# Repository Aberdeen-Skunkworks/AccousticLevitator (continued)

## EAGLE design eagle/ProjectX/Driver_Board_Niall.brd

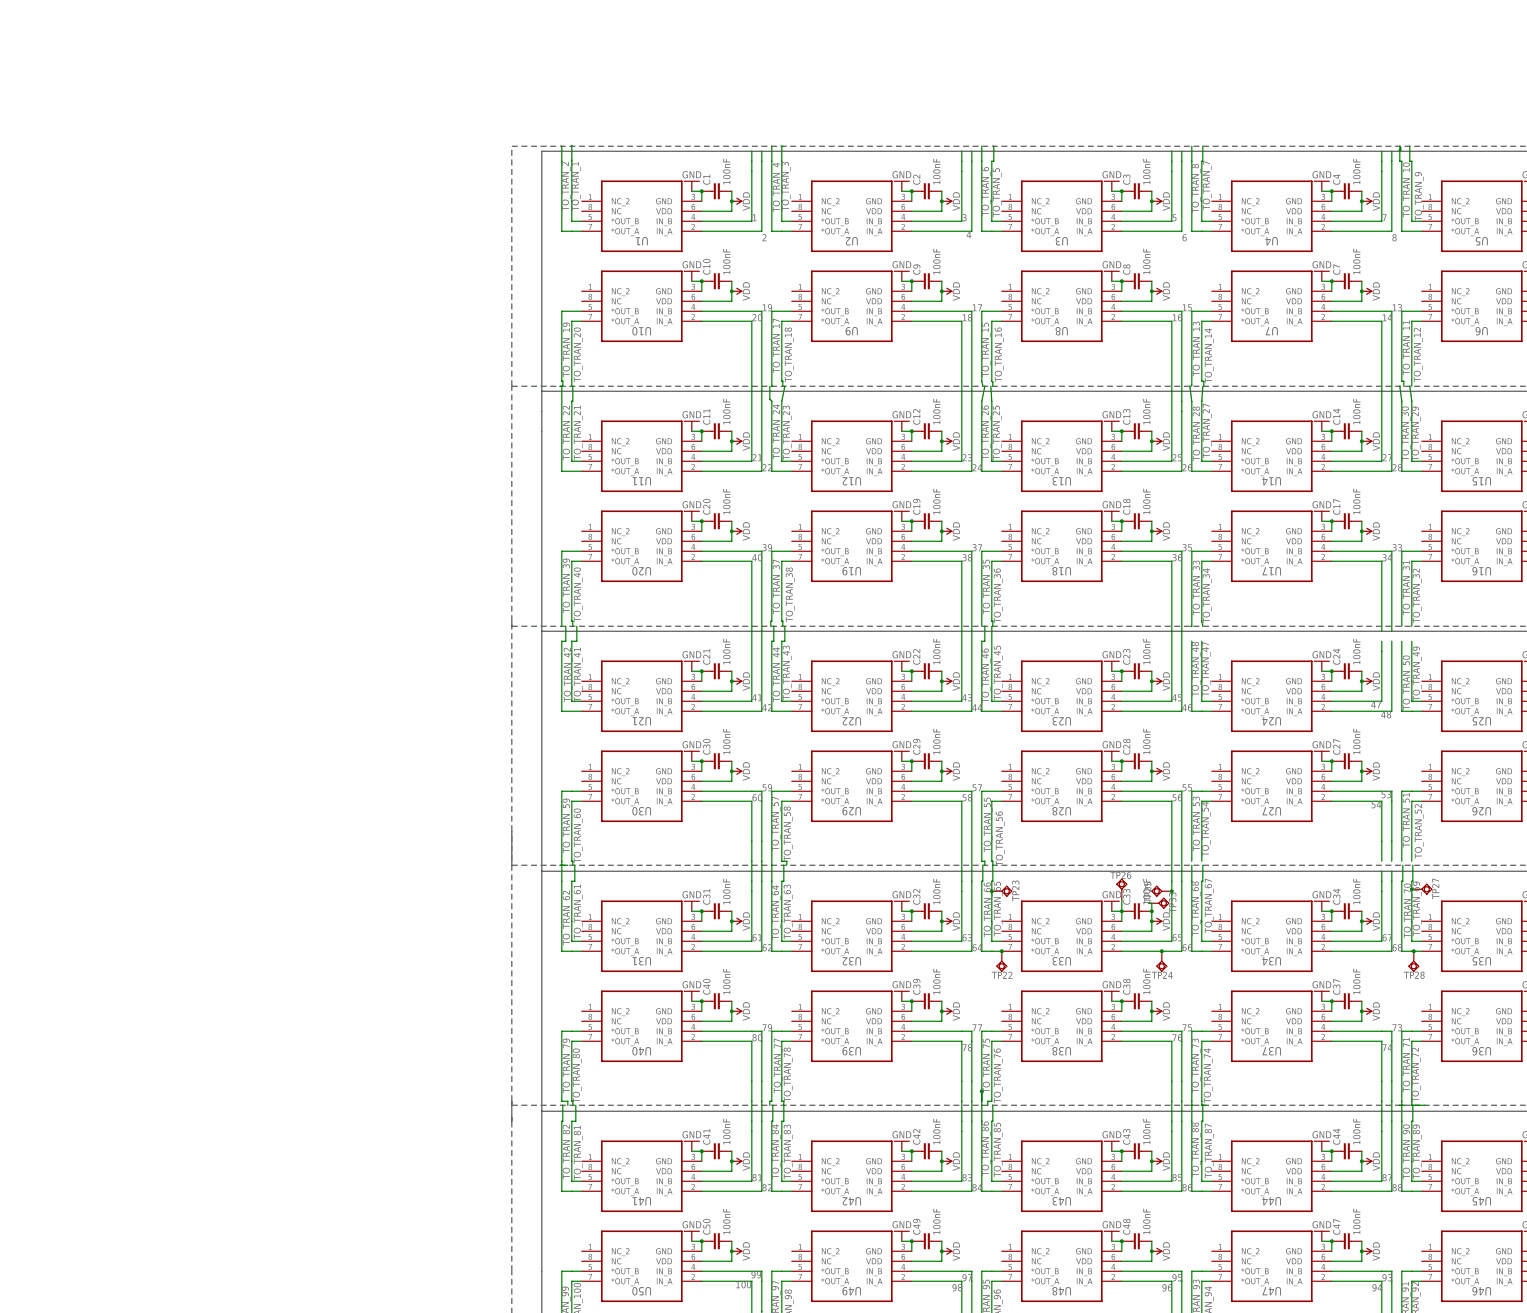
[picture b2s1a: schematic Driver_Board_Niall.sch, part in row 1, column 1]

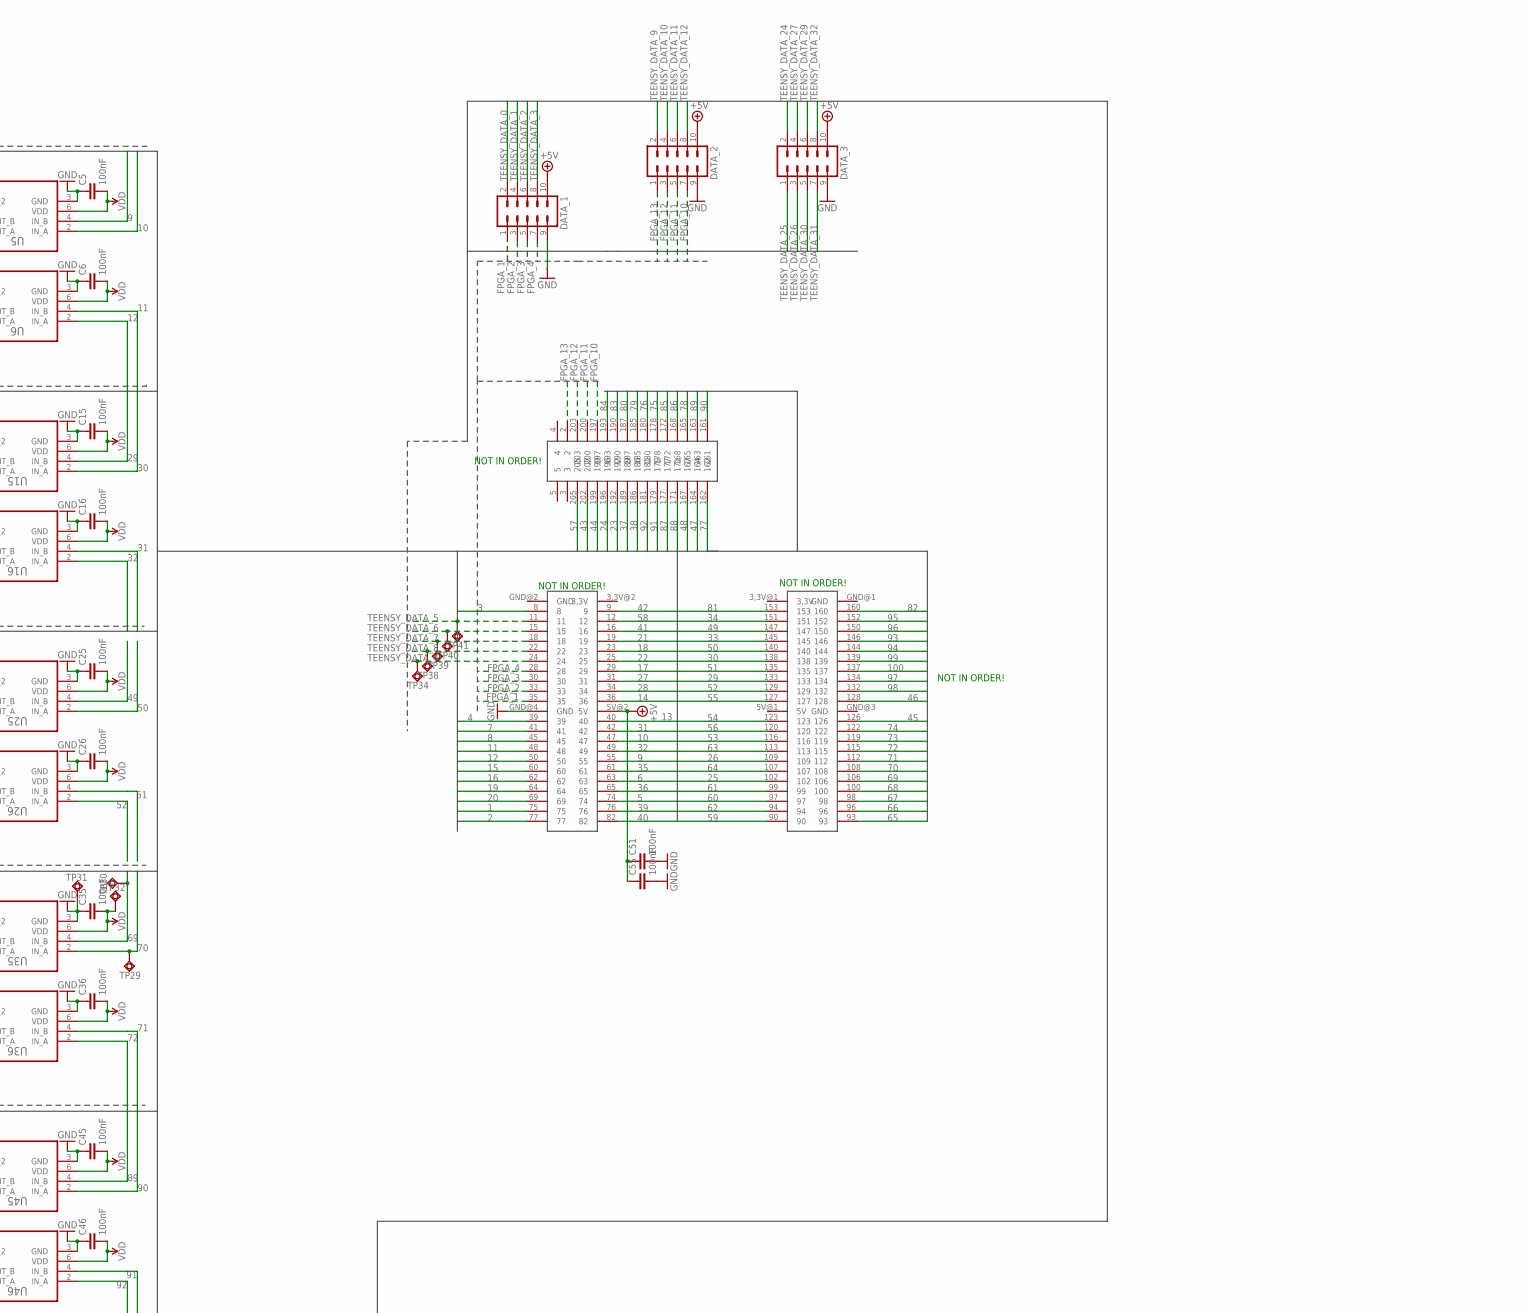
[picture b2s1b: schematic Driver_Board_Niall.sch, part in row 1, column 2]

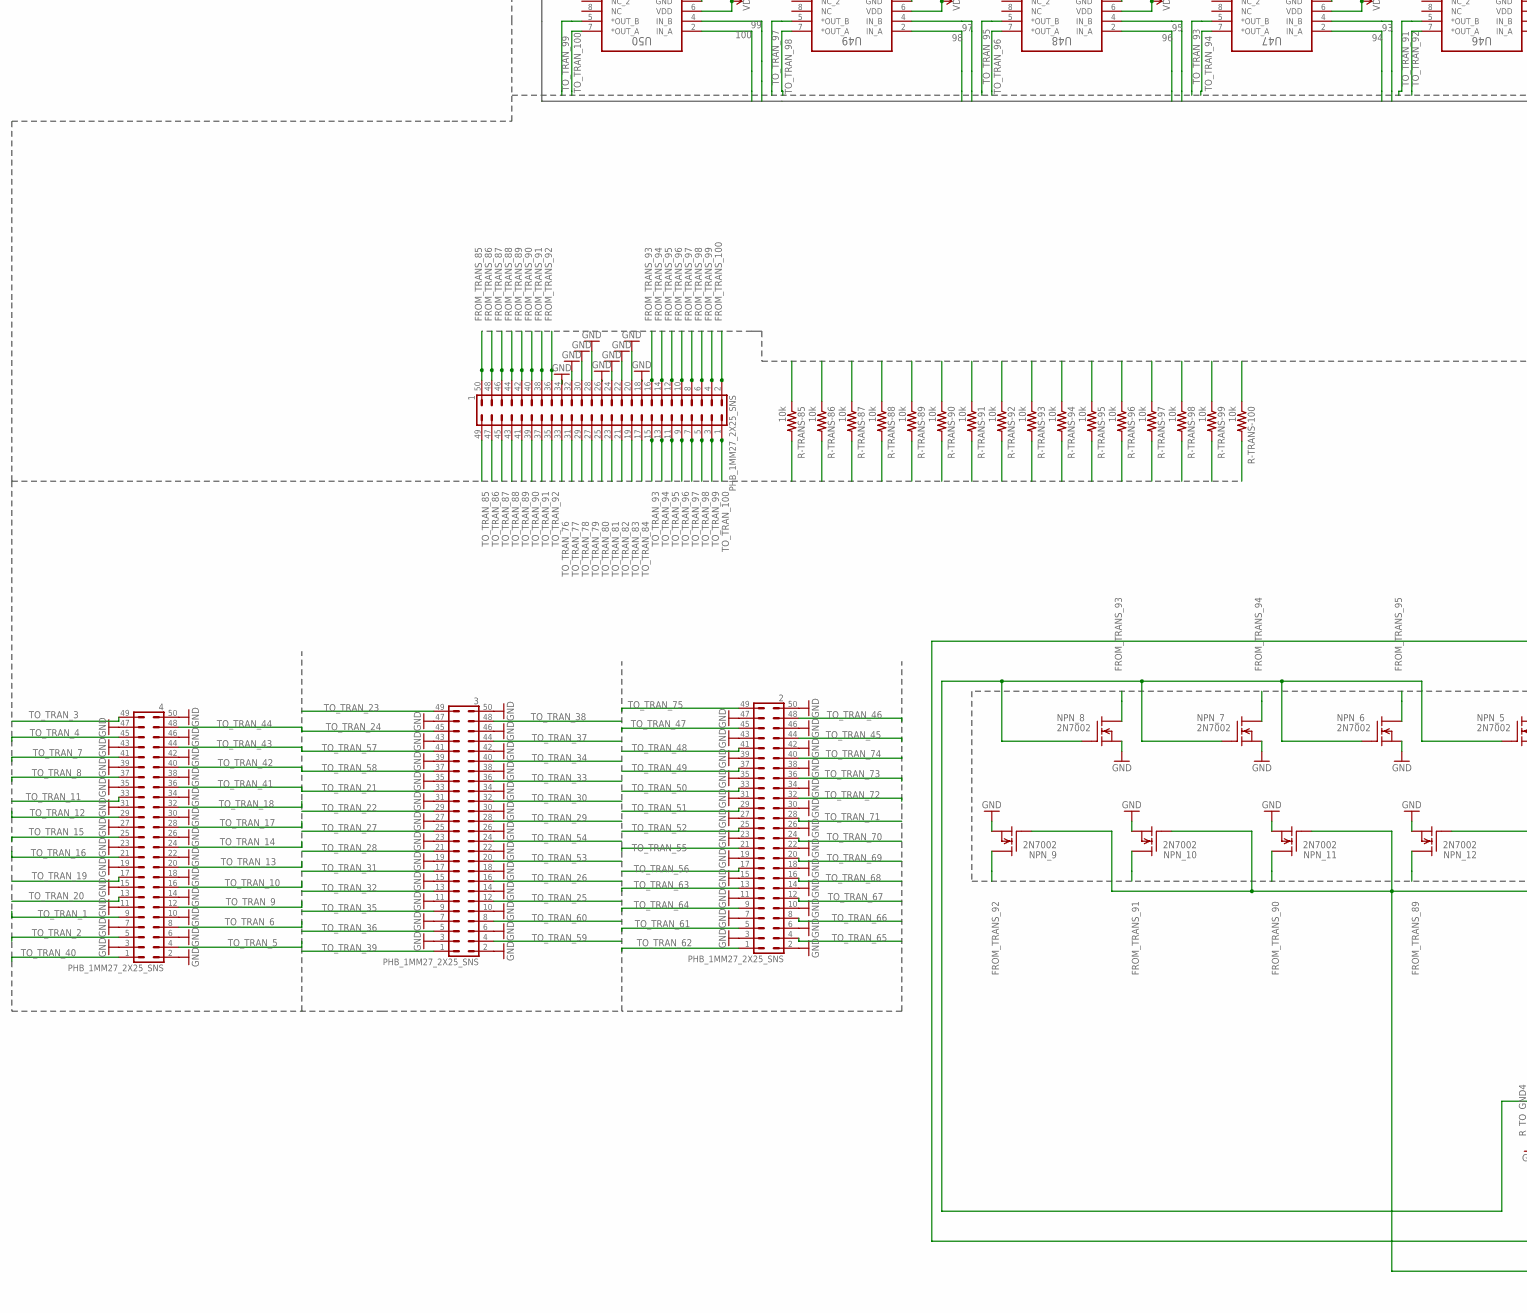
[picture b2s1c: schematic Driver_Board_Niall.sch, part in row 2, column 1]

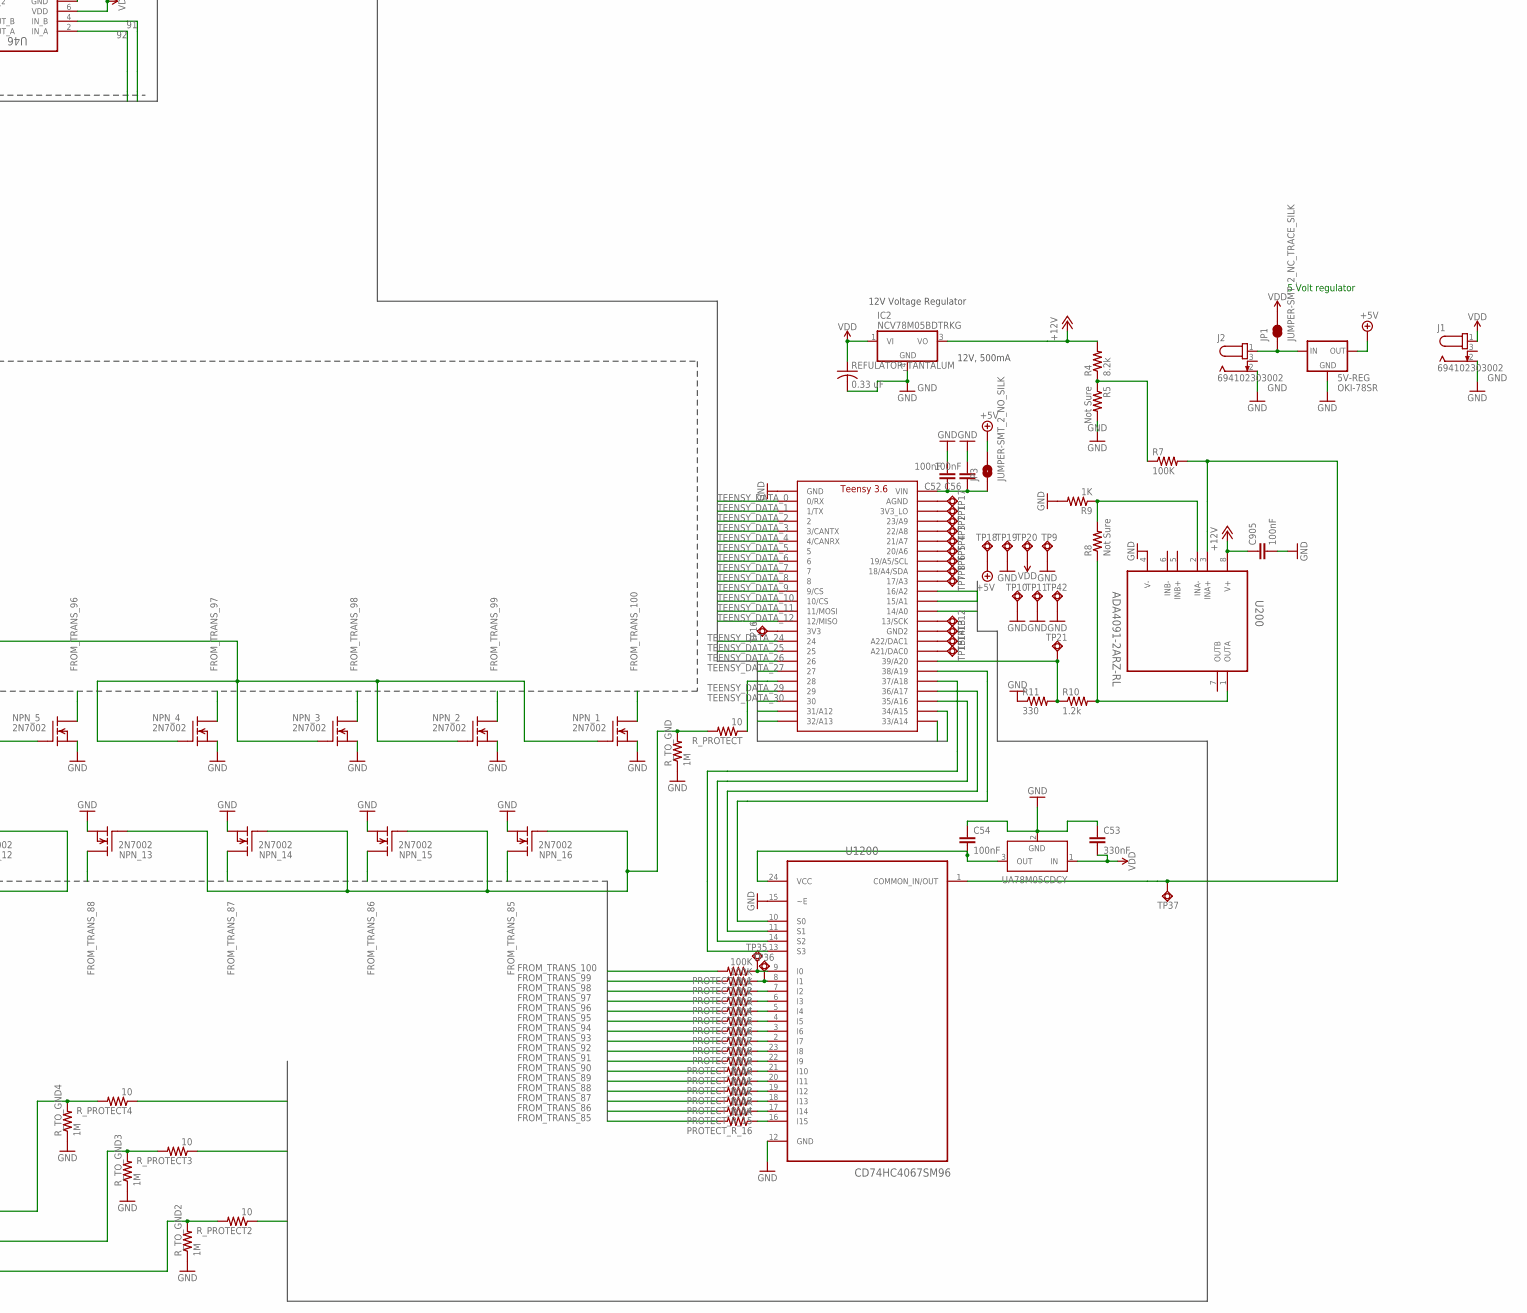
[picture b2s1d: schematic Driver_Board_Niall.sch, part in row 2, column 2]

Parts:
1, 2, 3, 4: PHB_1MM27_2X25_SNS
5V-REG: OKI-78SR; OKI-78SR-HORIZ
C1, C2, C3, C4, C5, C6, C7, C8, C9, C10, C11, C12, C13, C14, C15, C16, C17, C18, C19, C20, C21, C22, C23, C24, C25, C26, C27, C28, C29, C30, C31, C32, C33, C34, C35, C36, C37, C38, C39, C40, C41, C42, C43, C44, C45, C46, C47, C48, C49, C50, C51, C52, C54, C55, C56, C905: 100nF; C0805
C53: 330nF; C0805
DATA_1, DATA_2, DATA_3: MA05-2
DIP2: CORE3S500ESMT; CORE3S500E-SMT
IC2: NCV78M05BDTRKG; DPACK_3
J1, J2: 694102303002; 69410X303002
JP1: JUMPER-SMT_2_NC_TRACE_SILK; SMT-JUMPER_2_NC_TRACE_SILK
JP3: JUMPER-SMT_2_NO_SILK; SMT-JUMPER_2_NO_SILK
NPN_1, NPN_2, NPN_3, NPN_4, NPN_5, NPN_6, NPN_7, NPN_8, NPN_9, NPN_10, NPN_11, NPN_12, NPN_13, NPN_14, NPN_15, NPN_16: 2N7002; SOT23
PROTECT_R_1, PROTECT_R_2, PROTECT_R_3, PROTECT_R_4, PROTECT_R_5, PROTECT_R_6, PROTECT_R_7, PROTECT_R_8, PROTECT_R_9, PROTECT_R_10, PROTECT_R_11, PROTECT_R_12, PROTECT_R_13, PROTECT_R_14, PROTECT_R_15, PROTECT_R_16: 100K; M0805
R4: 8.2k; M0805
R5, R8: Not Sure; M0805
R7: 100K; M0805
R9: 1K; M0805
R10: 1.2k; M0805
R11: 330; M0805
R-TRANS-85, R-TRANS-86, R-TRANS-87, R-TRANS-88, R-TRANS-89, R-TRANS-90, R-TRANS-91, R-TRANS-92, R-TRANS-93, R-TRANS-94, R-TRANS-95, R-TRANS-96, R-TRANS-97, R-TRANS-98, R-TRANS-99, R-TRANS-100: 10k; M0805
REFULATOR_TANTALUM: 0.33 uF; C1206
R_PROTECT, R_PROTECT2, R_PROTECT3, R_PROTECT4: 10; M0805
R_TO_GND, R_TO_GND2, R_TO_GND3, R_TO_GND4: 1M; M0805
TP1, TP2, TP3, TP4, TP5, TP6, TP7, TP8, TP9, TP10, TP11, TP12, TP13, TP14, TP15, TP16, TP17, TP18, TP19, TP20, TP21, TP22, TP23, TP24, TP25, TP26, TP27, TP28, TP29, TP30, TP31, TP32, TP33, TP34, TP35, TP36, TP37, TP38, TP39, TP40, TP41, TP42: TPSQPAD1-13; P1-13
U1, U2, U3, U4, U5, U6, U7, U8, U9, U10, U11, U12, U13, U14, U15, U16, U17, U18, U19, U20, U21, U22, U23, U24, U25, U26, U27, U28, U29, U30, U31, U32, U33, U34, U35, U36, U37, U38, U39, U40, U41, U42, U43, U44, U45, U46, U47, U48, U49, U50: TC4427AEOA; SOIC127P600X175-8N
U200: ADA4091-2ARZ-RL; ADA4091-2ARZ-RL_SOIC127P600X175-8N
U1200: CD74HC4067SM96; SOP65P780X200-24N
U$1: TEENSY_SMD; TEENSY_3.6_SMD
UA78M05CDCY: LT1129CST5; SOT223

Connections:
1: DIP2.75, U1.4 (IN_B)
2: DIP2.77, U1.2 (IN_A)
3: DIP2.8, U2.4 (IN_B)
4: DIP2.39, U2.2 (IN_A)
5: DIP2.74, U3.4 (IN_B)
6: DIP2.63, U3.2 (IN_A)
7: DIP2.41, U4.4 (IN_B)
8: DIP2.45, U4.2 (IN_A)
9: DIP2.55, U5.4 (IN_B)
10: DIP2.47, U5.2 (IN_A)
11: DIP2.48, U6.4 (IN_B)
12: DIP2.50, U6.2 (IN_A)
13: DIP2.40, U7.4 (IN_B)
14: DIP2.36, U7.2 (IN_A)
15: DIP2.60, U8.4 (IN_B)
16: DIP2.62, U8.2 (IN_A)
17: DIP2.29, U9.4 (IN_B)
18: DIP2.23, U9.2 (IN_A)
19: DIP2.64, U10.4 (IN_B)
20: DIP2.69, U10.2 (IN_A)
21: DIP2.19, U11.4 (IN_B)
22: DIP2.25, U11.2 (IN_A)
23: DIP2.192, U12.4 (IN_B)
24: DIP2.196, U12.2 (IN_A)
25: DIP2.102, U13.4 (IN_B)
26: DIP2.109, U13.2 (IN_A)
27: DIP2.31, U14.4 (IN_B)
28: DIP2.34, U14.2 (IN_A)
29: DIP2.133, U15.4 (IN_B)
30: DIP2.138, U15.2 (IN_A)
31: DIP2.42, U16.4 (IN_B)
32: DIP2.49, U16.2 (IN_A)
33: DIP2.145, U17.4 (IN_B)
34: DIP2.151, U17.2 (IN_A)
35: DIP2.61, U18.4 (IN_B)
36: DIP2.65, U18.2 (IN_A)
37: DIP2.189, U19.4 (IN_B)
38: DIP2.186, U19.2 (IN_A)
39: DIP2.76, U20.4 (IN_B)
40: DIP2.82, U20.2 (IN_A)
41: DIP2.16, U21.4 (IN_B)
42: DIP2.9, U21.2 (IN_A)
43: DIP2.202, U22.4 (IN_B)
44: DIP2.199, U22.2 (IN_A)
45: DIP2.126, U23.4 (IN_B)
46: DIP2.128, U23.2 (IN_A)
47: DIP2.164, U24.4 (IN_B)
48: DIP2.167, U24.2 (IN_A)
49: DIP2.147, U25.4 (IN_B)
50: DIP2.140, U25.2 (IN_A)
51: DIP2.135, U26.4 (IN_B)
52: DIP2.129, U26.2 (IN_A)
53: DIP2.116, U27.4 (IN_B)
54: DIP2.123, U27.2 (IN_A)
55: DIP2.127, U28.4 (IN_B)
56: DIP2.120, U28.2 (IN_A)
57: DIP2.205, U29.4 (IN_B)
58: DIP2.12, U29.2 (IN_A)
59: DIP2.90, U30.4 (IN_B)
60: DIP2.97, U30.2 (IN_A)
61: DIP2.99, U31.4 (IN_B)
62: DIP2.94, U31.2 (IN_A)
63: DIP2.113, U32.4 (IN_B)
64: DIP2.107, U32.2 (IN_A)
65: DIP2.93, TP25.TP, U33.4 (IN_B)
66: DIP2.96, TP24.TP, U33.2 (IN_A)
67: DIP2.98, U34.4 (IN_B)
68: DIP2.100, U34.2 (IN_A)
69: DIP2.106, TP30.TP, U35.4 (IN_B)
70: DIP2.108, TP29.TP, U35.2 (IN_A)
71: DIP2.112, U36.4 (IN_B)
72: DIP2.115, U36.2 (IN_A)
73: DIP2.119, U37.4 (IN_B)
74: DIP2.122, U37.2 (IN_A)
75: DIP2.178, U38.4 (IN_B)
76: DIP2.180, U38.2 (IN_A)
77: DIP2.162, U39.4 (IN_B)
78: DIP2.165, U39.2 (IN_A)
79: DIP2.185, U40.4 (IN_B)
80: DIP2.187, U40.2 (IN_A)
81: DIP2.153, U41.4 (IN_B)
82: DIP2.160, U41.2 (IN_A)
83: DIP2.190, U42.4 (IN_B)
84: DIP2.193, U42.2 (IN_A)
85: DIP2.172, U43.4 (IN_B)
86: DIP2.168, U43.2 (IN_A)
87: DIP2.177, U44.4 (IN_B)
88: DIP2.171, U44.2 (IN_A)
89: DIP2.163, U45.4 (IN_B)
90: DIP2.161, U45.2 (IN_A)
91: DIP2.179, U46.4 (IN_B)
92: DIP2.181, U46.2 (IN_A)
93: DIP2.146, U47.4 (IN_B)
94: DIP2.144, U47.2 (IN_A)
95: DIP2.152, U48.4 (IN_B)
96: DIP2.150, U48.2 (IN_A)
97: DIP2.134, U49.4 (IN_B)
98: DIP2.132, U49.2 (IN_A)
99: DIP2.139, U50.4 (IN_B)
100: DIP2.137, U50.2 (IN_A)
+5V: 5V-REG.OUT, C51.1, C55.1, DATA_1.10, DATA_2.10, DATA_3.10, DIP2.5V@2 (5V), JP3.2, TP18.TP
+12V: C905.1, IC2.3 (VO), R4.2, U200.8 (V+)
FET_2: R_PROTECT2.1, U$1.16/A4 (16/A2)
FET_3: R_PROTECT3.1, U$1.15/A4 (15/A1)
FET_4: R_PROTECT4.1, U$1.14/A3 (14/A0)
FPGA_1: DATA_1.1, DIP2.35
FPGA_2: DATA_1.3, DIP2.33
FPGA_3: DATA_1.5, DIP2.30
FPGA_4: DATA_1.7, DIP2.28
FPGA_10: DATA_2.7, DIP2.197
FPGA_11: DATA_2.5, DIP2.200
FPGA_12: DATA_2.3, DIP2.203
FPGA_13: DATA_2.1, DIP2.2
FROM_TRANS_85: 1.50, NPN_16.3 (D), PROTECT_R_16.2, R-TRANS-85.1
FROM_TRANS_86: 1.48, NPN_15.3 (D), PROTECT_R_15.2, R-TRANS-86.1
FROM_TRANS_87: 1.46, NPN_14.3 (D), PROTECT_R_14.2, R-TRANS-87.1
FROM_TRANS_88: 1.44, NPN_13.3 (D), PROTECT_R_13.2, R-TRANS-88.1
FROM_TRANS_89: 1.42, NPN_12.3 (D), PROTECT_R_12.2, R-TRANS-89.1
FROM_TRANS_90: 1.40, NPN_11.3 (D), PROTECT_R_11.2, R-TRANS-90.1
FROM_TRANS_91: 1.38, NPN_10.3 (D), PROTECT_R_10.2, R-TRANS-91.1
FROM_TRANS_92: 1.36, NPN_9.3 (D), PROTECT_R_9.2, R-TRANS-92.1
FROM_TRANS_93: 1.16, NPN_8.3 (D), PROTECT_R_8.2, R-TRANS-93.1
FROM_TRANS_94: 1.14, NPN_7.3 (D), PROTECT_R_7.2, R-TRANS-94.1
FROM_TRANS_95: 1.12, NPN_6.3 (D), PROTECT_R_6.2, R-TRANS-95.1
FROM_TRANS_96: 1.10, NPN_5.3 (D), PROTECT_R_5.2, R-TRANS-96.1
FROM_TRANS_97: 1.8, NPN_4.3 (D), PROTECT_R_4.2, R-TRANS-97.1
FROM_TRANS_98: 1.6, NPN_3.3 (D), PROTECT_R_3.2, R-TRANS-98.1
FROM_TRANS_99: 1.4, NPN_2.3 (D), PROTECT_R_2.2, R-TRANS-99.1
FROM_TRANS_100: 1.2, NPN_1.3 (D), PROTECT_R_1.2, R-TRANS-100.1
GND: 1.18, 1.20, 1.22, 1.24, 1.26, 1.28, 1.30, 1.32, 1.34, 2.2, 2.3, 2.6, 2.7, 2.10, 2.11, 2.14, 2.15, 2.18, 2.19, 2.22, 2.23, 2.26, 2.27, 2.30, 2.31, 2.34, 2.35, 2.38, 2.39, 2.42, 2.43, 2.46, 2.47, 2.50, 3.2, 3.3, 3.6, 3.7, 3.10, 3.11, 3.14, 3.15, 3.18, 3.19, 3.22, 3.23, 3.26, 3.27, 3.30, 3.31, 3.34, 3.35, 3.38, 3.39, 3.42, 3.43, 3.46, 3.47, 3.50, 4.2, 4.3, 4.6, 4.7, 4.10, 4.11, 4.14, 4.15, 4.18, 4.19, 4.22, 4.23, 4.26, 4.27, 4.30, 4.31, 4.34, 4.35, 4.38, 4.39, 4.42, 4.43, 4.46, 4.47, 4.50, 5V-REG.GND, C1.1, C2.1, C3.1, C4.1, C5.1, C6.1, C7.1, C8.1, C9.1, C10.1, C11.1, C12.1, C13.1, C14.1, C15.1, C16.1, C17.1, C18.1, C19.1, C20.1, C21.1, C22.1, C23.1, C24.1, C25.1, C26.1, C27.1, C28.1, C29.1, C30.1, C31.1, C32.1, C33.1, C34.1, C35.1, C36.1, C37.1, C38.1, C39.1, C40.1, C41.1, C42.1, C43.1, C44.1, C45.1, C46.1, C47.1, C48.1, C49.1, C50.1, C51.2, C52.2, C53.1, C54.1, C55.2, C56.2, C905.2, DATA_1.9, DATA_2.9, DATA_3.9, DIP2.GND@4 (GND), IC2.4 (GND), J1.2, J2.2, NPN_1.2 (S), NPN_2.2 (S), NPN_3.2 (S), NPN_4.2 (S), NPN_5.2 (S), NPN_6.2 (S), NPN_7.2 (S), NPN_8.2 (S), NPN_9.2 (S), NPN_10.2 (S), NPN_11.2 (S), NPN_12.2 (S), NPN_13.2 (S), NPN_14.2 (S), NPN_15.2 (S), NPN_16.2 (S), R5.2, R9.2, R11.1, REFULATOR_TANTALUM.2, R_TO_GND.1, R_TO_GND2.1, R_TO_GND3.1, R_TO_GND4.1, TP9.TP, TP10.TP, TP11.TP, TP19.TP, TP26.TP, TP31.TP, TP42.TP, U1.3 (GND), U2.3 (GND), U3.3 (GND), U4.3 (GND), U5.3 (GND), U6.3 (GND), U7.3 (GND), U8.3 (GND), U9.3 (GND), U10.3 (GND), U11.3 (GND), U12.3 (GND), U13.3 (GND), U14.3 (GND), U15.3 (GND), U16.3 (GND), U17.3 (GND), U18.3 (GND), U19.3 (GND), U20.3 (GND), U21.3 (GND), U22.3 (GND), U23.3 (GND), U24.3 (GND), U25.3 (GND), U26.3 (GND), U27.3 (GND), U28.3 (GND), U29.3 (GND), U30.3 (GND), U31.3 (GND), U32.3 (GND), U33.3 (GND), U34.3 (GND), U35.3 (GND), U36.3 (GND), U37.3 (GND), U38.3 (GND), U39.3 (GND), U40.3 (GND), U41.3 (GND), U42.3 (GND), U43.3 (GND), U44.3 (GND), U45.3 (GND), U46.3 (GND), U47.3 (GND), U48.3 (GND), U49.3 (GND), U50.3 (GND), U200.4 (V-), U1200.12 (GND), U1200.15 (~E), U$1.GND6 (GND), UA78M05CDCY.2 (GND), UA78M05CDCY.4 (GND)
unnamed: PROTECT_R_1.1, TP35.TP, U1200.9 (I0)
unnamed: R4.1, R5.1, R7.1
unnamed: PROTECT_R_2.1, TP36.TP, U1200.8 (I1)
unnamed: R10.1, R11.2, TP21.TP, U$1.39/A3 (39/A20)
unnamed: U1200.10 (S0), U$1.38/A3 (38/A19)
unnamed: R8.1, R10.2, U200.1 (OUTA)
unnamed: R_PROTECT.1, U$1.28
unnamed: TP1.TP, U$1.3V3_LO3 (3V3_LO)
unnamed: U1200.13 (S3), U$1.37/A3 (37/A18)
unnamed: U1200.14 (S2), U$1.35/A3 (35/A16)
unnamed: U1200.11 (S1), U$1.36/A3 (36/A17)
unnamed: TP2.TP, U$1.23/A3 (23/A9)
unnamed: R8.2, R9.1, U200.2 (INA-)
unnamed: TP3.TP, U$1.22/A3 (22/A8)
unnamed: TP4.TP, U$1.21/A3 (21/A7)
unnamed: TP5.TP, U$1.20/A3 (20/A6)
unnamed: TP6.TP, U$1.19/A5/SCL3 (19/A5/SCL)
unnamed: TP7.TP, U$1.17/A4 (17/A3)
unnamed: TP8.TP, U$1.18/A4/SDA3 (18/A4/SDA)
unnamed: NPN_1.1 (G), NPN_2.1 (G), NPN_3.1 (G), NPN_4.1 (G), R_PROTECT3.2, R_TO_GND3.2
unnamed: C54.2, U1200.24 (VCC), UA78M05CDCY.3 (OUT)
unnamed: 5V-REG.IN, J2.1, JP1.1
unnamed: C52.1, C56.1, JP3.1, U$1.VIN3 (VIN)
unnamed: NPN_5.1 (G), NPN_6.1 (G), NPN_7.1 (G), NPN_8.1 (G), R_PROTECT4.2, R_TO_GND4.2
unnamed: TP12.TP, U$1.13/SCK3 (13/SCK)
unnamed: TP13.TP, U$1.GND7 (GND2)
unnamed: TP14.TP, U$1.A22/DAC1
unnamed: TP15.TP, U$1.A21/DAC0
unnamed: TP16.TP, U$1.3V4 (3V3)
unnamed: R7.2, TP37.TP, U200.3 (INA+), U1200.1 (COMMON_IN/OUT)
unnamed: TP17.TP, U$1.AGND3 (AGND)
unnamed: PROTECT_R_3.1, U1200.7 (I2)
unnamed: NPN_13.1 (G), NPN_14.1 (G), NPN_15.1 (G), NPN_16.1 (G), R_PROTECT.2, R_TO_GND.2
unnamed: NPN_9.1 (G), NPN_10.1 (G), NPN_11.1 (G), NPN_12.1 (G), R_PROTECT2.2, R_TO_GND2.2
unnamed: PROTECT_R_4.1, U1200.6 (I3)
unnamed: PROTECT_R_5.1, U1200.5 (I4)
unnamed: PROTECT_R_6.1, U1200.4 (I5)
unnamed: PROTECT_R_7.1, U1200.3 (I6)
unnamed: PROTECT_R_8.1, U1200.2 (I7)
unnamed: PROTECT_R_9.1, U1200.23 (I8)
unnamed: PROTECT_R_10.1, U1200.22 (I9)
unnamed: PROTECT_R_11.1, U1200.21 (I10)
unnamed: PROTECT_R_12.1, U1200.20 (I11)
unnamed: PROTECT_R_13.1, U1200.19 (I12)
unnamed: PROTECT_R_14.1, U1200.18 (I13)
unnamed: PROTECT_R_15.1, U1200.17 (I14)
unnamed: PROTECT_R_16.1, U1200.16 (I15)
TEENSY_DATA_0: DATA_1.2, U$1.0/RX3 (0/RX)
TEENSY_DATA_1: DATA_1.4, U$1.1/TX3 (1/TX)
TEENSY_DATA_2: DATA_1.6, U$1.2
TEENSY_DATA_3: DATA_1.8, U$1.3/CANTX3 (3/CANTX)
TEENSY_DATA_4: DIP2.24, TP34.TP, U$1.4/CANRX3 (4/CANRX)
TEENSY_DATA_5: DIP2.11, TP41.TP, U$1.5
TEENSY_DATA_6: DIP2.15, TP40.TP, U$1.6
TEENSY_DATA_7: DIP2.18, TP39.TP, U$1.7
TEENSY_DATA_8: DIP2.22, TP38.TP, U$1.8
TEENSY_DATA_9: DATA_2.2, U$1.9/CS3 (9/CS)
TEENSY_DATA_10: DATA_2.4, U$1.10/CS3 (10/CS)
TEENSY_DATA_11: DATA_2.6, U$1.11/MOSI3 (11/MOSI)
TEENSY_DATA_12: DATA_2.8, U$1.12/MISO3 (12/MISO)
TEENSY_DATA_24: DATA_3.2, U$1.24
TEENSY_DATA_25: DATA_3.1, U$1.25
TEENSY_DATA_26: DATA_3.3, U$1.26
TEENSY_DATA_27: DATA_3.4, U$1.27
TEENSY_DATA_29: DATA_3.6, U$1.29
TEENSY_DATA_30: DATA_3.5, U$1.30
TEENSY_DATA_31: DATA_3.7, U$1.31/A3 (31/A12)
TEENSY_DATA_32: DATA_3.8, U$1.32/A3 (32/A13)
TEENSY_DATA_33: U$1.33/A3 (33/A14)
TEENSY_DATA_34: U$1.34/A3 (34/A15)
TO_TRAN_1: 4.9, U1.5 (*OUT_B)
TO_TRAN_2: 4.5, U1.7 (*OUT_A)
TO_TRAN_3: 4.49, U2.5 (*OUT_B)
TO_TRAN_4: 4.45, U2.7 (*OUT_A)
TO_TRAN_5: 4.4, U3.5 (*OUT_B)
TO_TRAN_6: 4.8, U3.7 (*OUT_A)
TO_TRAN_7: 4.41, U4.5 (*OUT_B)
TO_TRAN_8: 4.37, U4.7 (*OUT_A)
TO_TRAN_9: 4.12, U5.5 (*OUT_B)
TO_TRAN_10: 4.16, U5.7 (*OUT_A)
TO_TRAN_11: 4.33, U6.5 (*OUT_B)
TO_TRAN_12: 4.29, U6.7 (*OUT_A)
TO_TRAN_13: 4.20, U7.5 (*OUT_B)
TO_TRAN_14: 4.24, U7.7 (*OUT_A)
TO_TRAN_15: 4.25, U8.5 (*OUT_B)
TO_TRAN_16: 4.21, U8.7 (*OUT_A)
TO_TRAN_17: 4.28, U9.5 (*OUT_B)
TO_TRAN_18: 4.32, U9.7 (*OUT_A)
TO_TRAN_19: 4.17, U10.5 (*OUT_B)
TO_TRAN_20: 4.13, U10.7 (*OUT_A)
TO_TRAN_21: 3.33, U11.5 (*OUT_B)
TO_TRAN_22: 3.29, U11.7 (*OUT_A)
TO_TRAN_23: 3.49, U12.5 (*OUT_B)
TO_TRAN_24: 3.45, U12.7 (*OUT_A)
TO_TRAN_25: 3.12, U13.5 (*OUT_B)
TO_TRAN_26: 3.16, U13.7 (*OUT_A)
TO_TRAN_27: 3.25, U14.5 (*OUT_B)
TO_TRAN_28: 3.21, U14.7 (*OUT_A)
TO_TRAN_29: 3.28, U15.5 (*OUT_B)
TO_TRAN_30: 3.32, U15.7 (*OUT_A)
TO_TRAN_31: 3.17, U16.5 (*OUT_B)
TO_TRAN_32: 3.13, U16.7 (*OUT_A)
TO_TRAN_33: 3.36, U17.5 (*OUT_B)
TO_TRAN_34: 3.40, U17.7 (*OUT_A)
TO_TRAN_35: 3.9, U18.5 (*OUT_B)
TO_TRAN_36: 3.5, U18.7 (*OUT_A)
TO_TRAN_37: 3.44, U19.5 (*OUT_B)
TO_TRAN_38: 3.48, U19.7 (*OUT_A)
TO_TRAN_39: 3.1, U20.5 (*OUT_B)
TO_TRAN_40: 4.1, U20.7 (*OUT_A)
TO_TRAN_41: 4.36, U21.5 (*OUT_B)
TO_TRAN_42: 4.40, U21.7 (*OUT_A)
TO_TRAN_43: 4.44, U22.5 (*OUT_B)
TO_TRAN_44: 4.48, U22.7 (*OUT_A)
TO_TRAN_45: 2.44, U23.5 (*OUT_B)
TO_TRAN_46: 2.48, U23.7 (*OUT_A)
TO_TRAN_47: 2.45, U24.5 (*OUT_B)
TO_TRAN_48: 2.41, U24.7 (*OUT_A)
TO_TRAN_49: 2.37, U25.5 (*OUT_B)
TO_TRAN_50: 2.33, U25.7 (*OUT_A)
TO_TRAN_51: 2.29, U26.5 (*OUT_B)
TO_TRAN_52: 2.25, U26.7 (*OUT_A)
TO_TRAN_53: 3.20, U27.5 (*OUT_B)
TO_TRAN_54: 3.24, U27.7 (*OUT_A)
TO_TRAN_55: 2.21, U28.5 (*OUT_B)
TO_TRAN_56: 2.17, U28.7 (*OUT_A)
TO_TRAN_57: 3.41, U29.5 (*OUT_B)
TO_TRAN_58: 3.37, U29.7 (*OUT_A)
TO_TRAN_59: 3.4, U30.5 (*OUT_B)
TO_TRAN_60: 3.8, U30.7 (*OUT_A)
TO_TRAN_61: 2.5, U31.5 (*OUT_B)
TO_TRAN_62: 2.1, U31.7 (*OUT_A)
TO_TRAN_63: 2.13, U32.5 (*OUT_B)
TO_TRAN_64: 2.9, U32.7 (*OUT_A)
TO_TRAN_65: 2.4, TP23.TP, U33.5 (*OUT_B)
TO_TRAN_66: 2.8, TP22.TP, U33.7 (*OUT_A)
TO_TRAN_67: 2.12, U34.5 (*OUT_B)
TO_TRAN_68: 2.16, U34.7 (*OUT_A)
TO_TRAN_69: 2.20, TP27.TP, U35.5 (*OUT_B)
TO_TRAN_70: 2.24, TP28.TP, U35.7 (*OUT_A)
TO_TRAN_71: 2.28, U36.5 (*OUT_B)
TO_TRAN_72: 2.32, U36.7 (*OUT_A)
TO_TRAN_73: 2.36, U37.5 (*OUT_B)
TO_TRAN_74: 2.40, U37.7 (*OUT_A)
TO_TRAN_75: 2.49, U38.5 (*OUT_B)
TO_TRAN_76: 1.33, U38.7 (*OUT_A)
TO_TRAN_77: 1.31, U39.5 (*OUT_B)
TO_TRAN_78: 1.29, U39.7 (*OUT_A)
TO_TRAN_79: 1.27, U40.5 (*OUT_B)
TO_TRAN_80: 1.25, U40.7 (*OUT_A)
TO_TRAN_81: 1.23, U41.5 (*OUT_B)
TO_TRAN_82: 1.21, U41.7 (*OUT_A)
TO_TRAN_83: 1.19, U42.5 (*OUT_B)
TO_TRAN_84: 1.17, U42.7 (*OUT_A)
TO_TRAN_85: 1.49, R-TRANS-85.2, U43.5 (*OUT_B)
TO_TRAN_86: 1.47, R-TRANS-86.2, U43.7 (*OUT_A)
TO_TRAN_87: 1.45, R-TRANS-87.2, U44.5 (*OUT_B)
TO_TRAN_88: 1.43, R-TRANS-88.2, U44.7 (*OUT_A)
TO_TRAN_89: 1.41, R-TRANS-89.2, U45.5 (*OUT_B)
TO_TRAN_90: 1.39, R-TRANS-90.2, U45.7 (*OUT_A)
TO_TRAN_91: 1.37, R-TRANS-91.2, U46.5 (*OUT_B)
TO_TRAN_92: 1.35, R-TRANS-92.2, U46.7 (*OUT_A)
TO_TRAN_93: 1.15, R-TRANS-93.2, U47.5 (*OUT_B)
TO_TRAN_94: 1.13, R-TRANS-94.2, U47.7 (*OUT_A)
TO_TRAN_95: 1.11, R-TRANS-95.2, U48.5 (*OUT_B)
TO_TRAN_96: 1.9, R-TRANS-96.2, U48.7 (*OUT_A)
TO_TRAN_97: 1.7, R-TRANS-97.2, U49.5 (*OUT_B)
TO_TRAN_98: 1.5, R-TRANS-98.2, U49.7 (*OUT_A)
TO_TRAN_99: 1.3, R-TRANS-99.2, U50.5 (*OUT_B)
TO_TRAN_100: 1.1, R-TRANS-100.2, U50.7 (*OUT_A)
VDD: C1.2, C2.2, C3.2, C4.2, C5.2, C6.2, C7.2, C8.2, C9.2, C10.2, C11.2, C12.2, C13.2, C14.2, C15.2, C16.2, C17.2, C18.2, C19.2, C20.2, C21.2, C22.2, C23.2, C24.2, C25.2, C26.2, C27.2, C28.2, C29.2, C30.2, C31.2, C32.2, C33.2, C34.2, C35.2, C36.2, C37.2, C38.2, C39.2, C40.2, C41.2, C42.2, C43.2, C44.2, C45.2, C46.2, C47.2, C48.2, C49.2, C50.2, C53.2, IC2.1 (VI), J1.1, JP1.2, REFULATOR_TANTALUM.1, TP20.TP, TP32.TP, TP33.TP, U1.6 (VDD), U2.6 (VDD), U3.6 (VDD), U4.6 (VDD), U5.6 (VDD), U6.6 (VDD), U7.6 (VDD), U8.6 (VDD), U9.6 (VDD), U10.6 (VDD), U11.6 (VDD), U12.6 (VDD), U13.6 (VDD), U14.6 (VDD), U15.6 (VDD), U16.6 (VDD), U17.6 (VDD), U18.6 (VDD), U19.6 (VDD), U20.6 (VDD), U21.6 (VDD), U22.6 (VDD), U23.6 (VDD), U24.6 (VDD), U25.6 (VDD), U26.6 (VDD), U27.6 (VDD), U28.6 (VDD), U29.6 (VDD), U30.6 (VDD), U31.6 (VDD), U32.6 (VDD), U33.6 (VDD), U34.6 (VDD), U35.6 (VDD), U36.6 (VDD), U37.6 (VDD), U38.6 (VDD), U39.6 (VDD), U40.6 (VDD), U41.6 (VDD), U42.6 (VDD), U43.6 (VDD), U44.6 (VDD), U45.6 (VDD), U46.6 (VDD), U47.6 (VDD), U48.6 (VDD), U49.6 (VDD), U50.6 (VDD), UA78M05CDCY.1 (IN)

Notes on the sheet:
12V Voltage Regulator
12V, 500mA
5 Volt regulator
NOT IN ORDER!

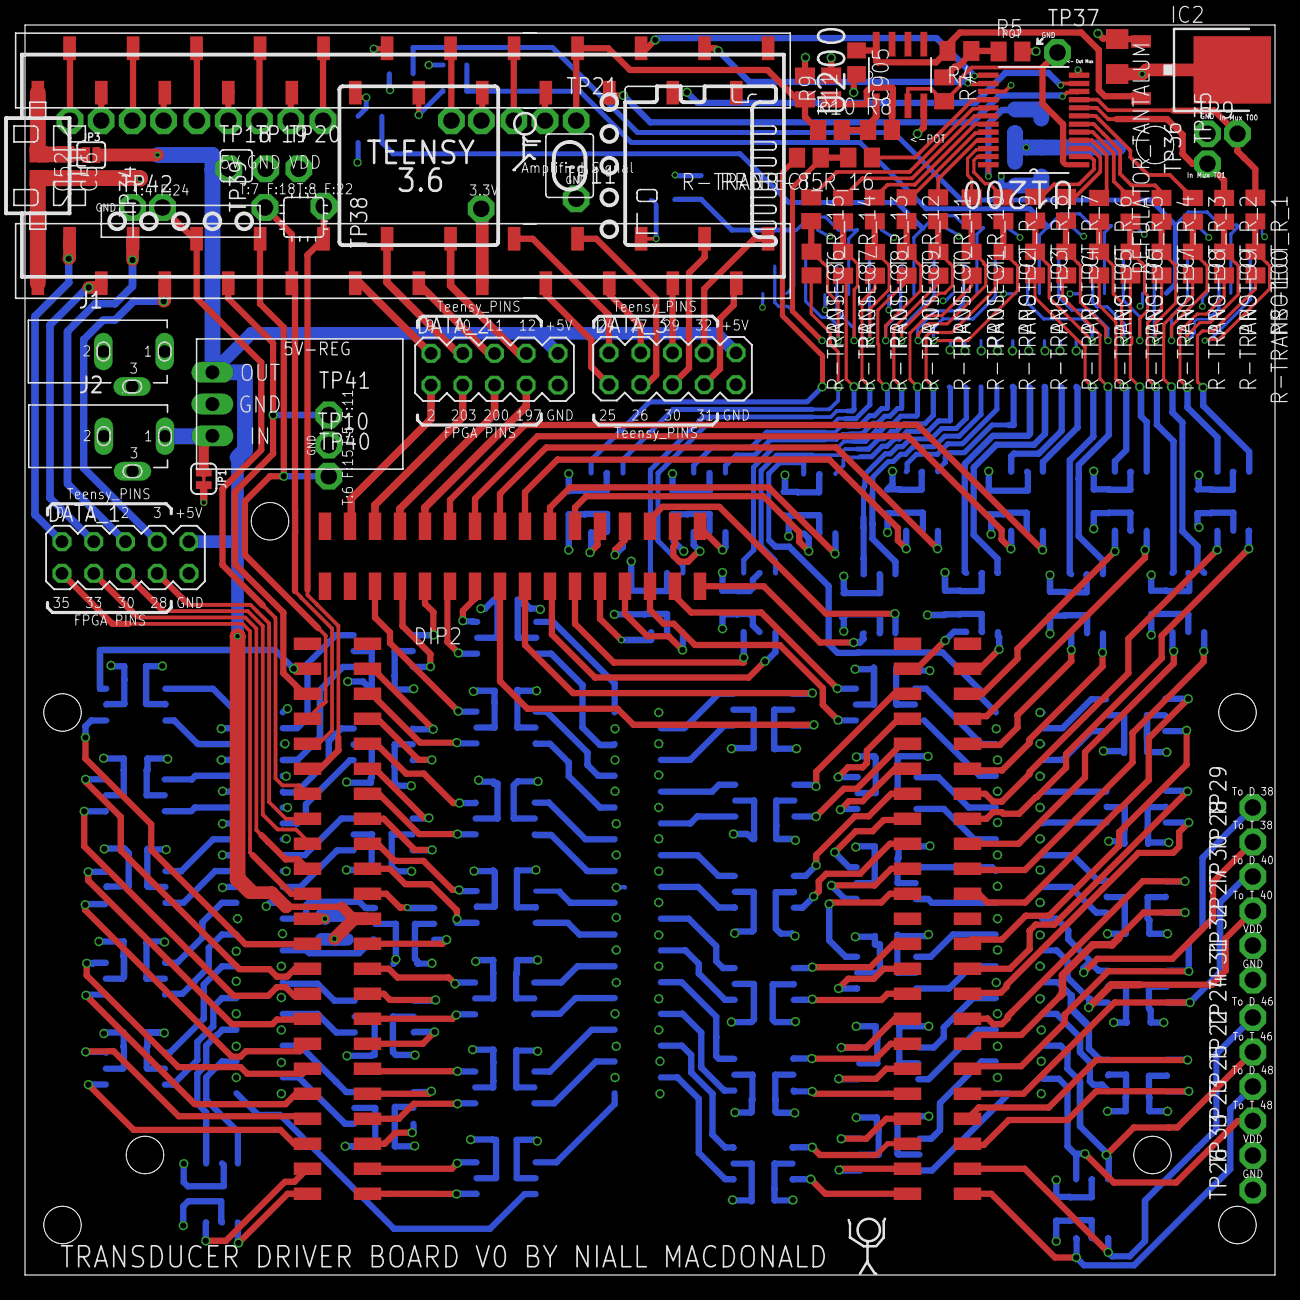
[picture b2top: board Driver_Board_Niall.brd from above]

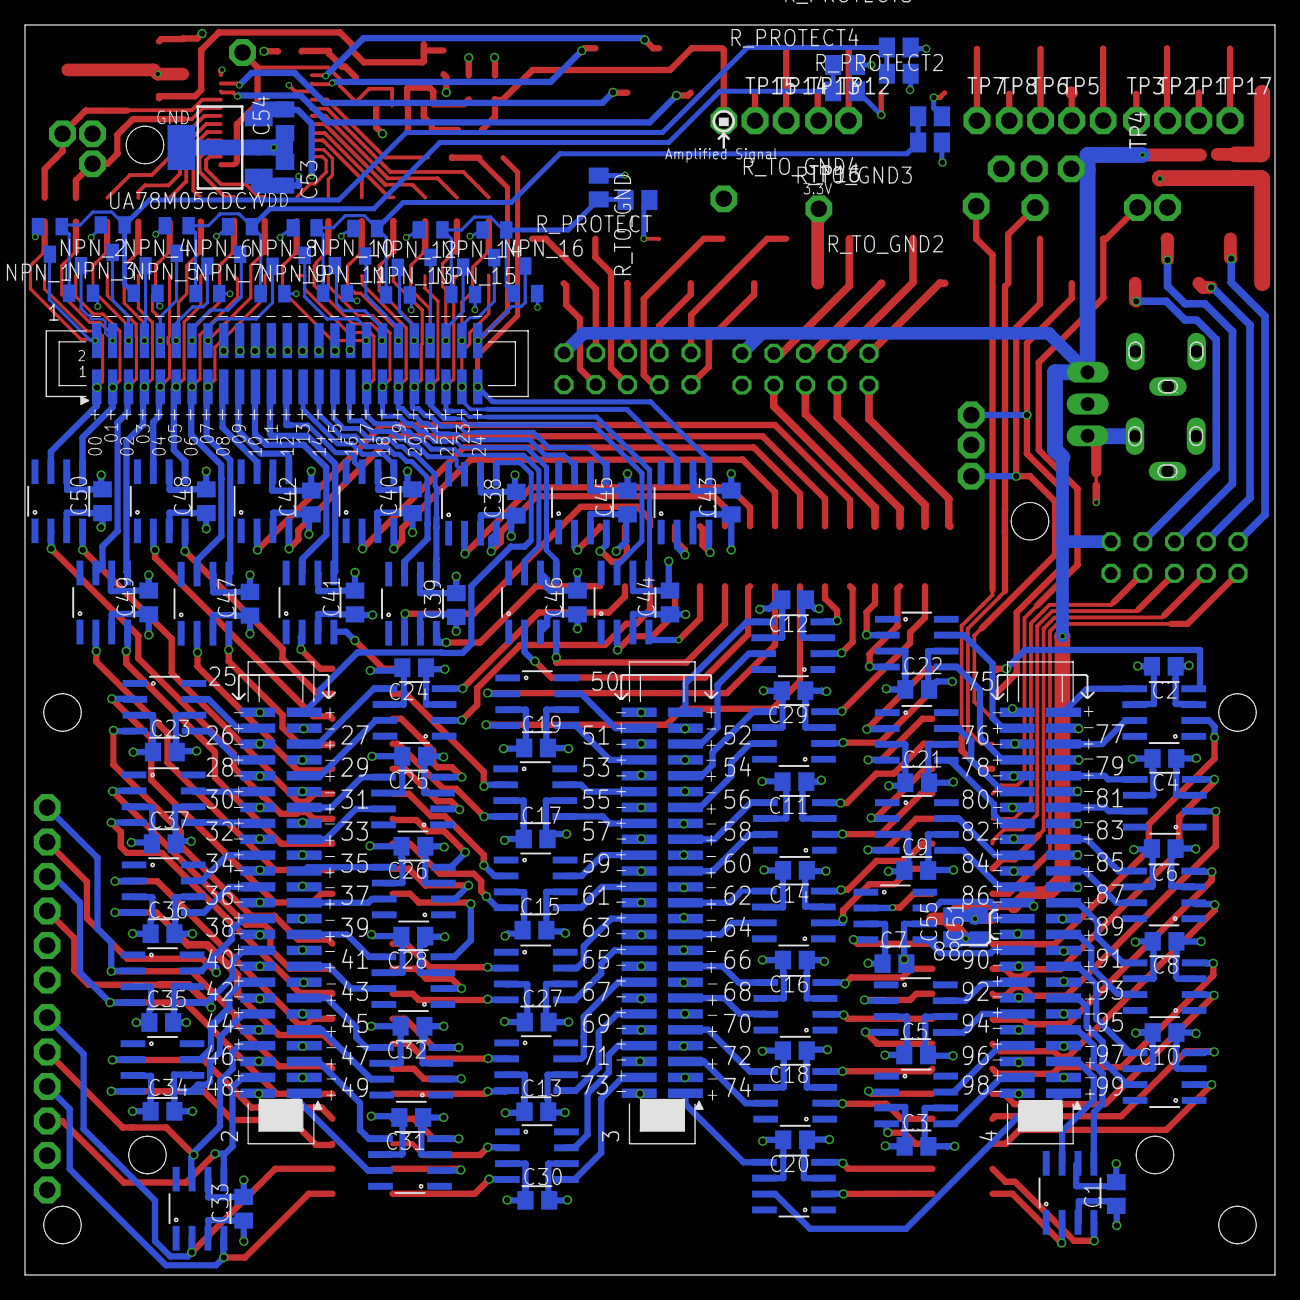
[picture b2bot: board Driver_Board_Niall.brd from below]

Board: 4 copper layers, 100.0 x 100.0 mm, 231 parts (147 on the bottom side), 299 nets.
